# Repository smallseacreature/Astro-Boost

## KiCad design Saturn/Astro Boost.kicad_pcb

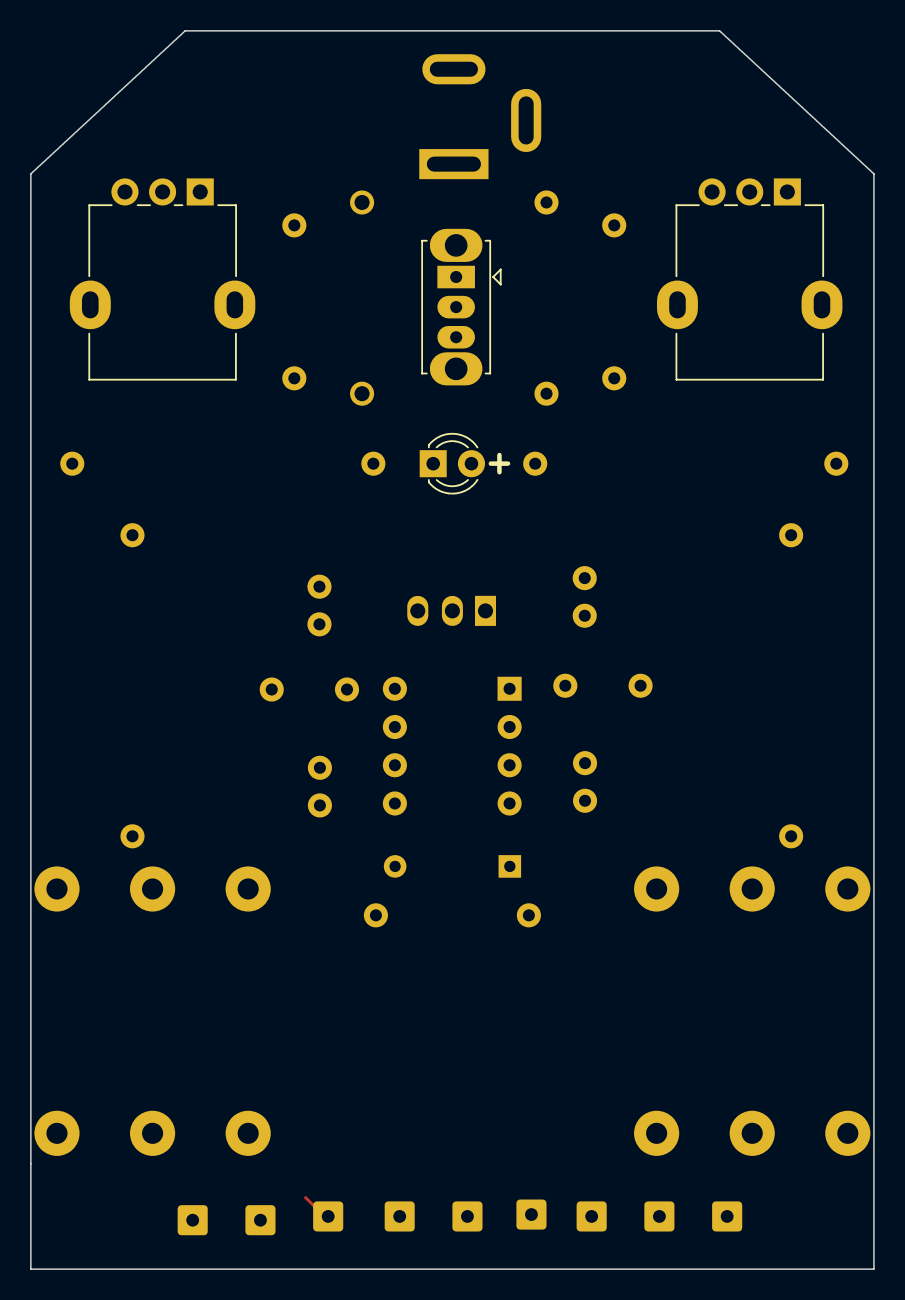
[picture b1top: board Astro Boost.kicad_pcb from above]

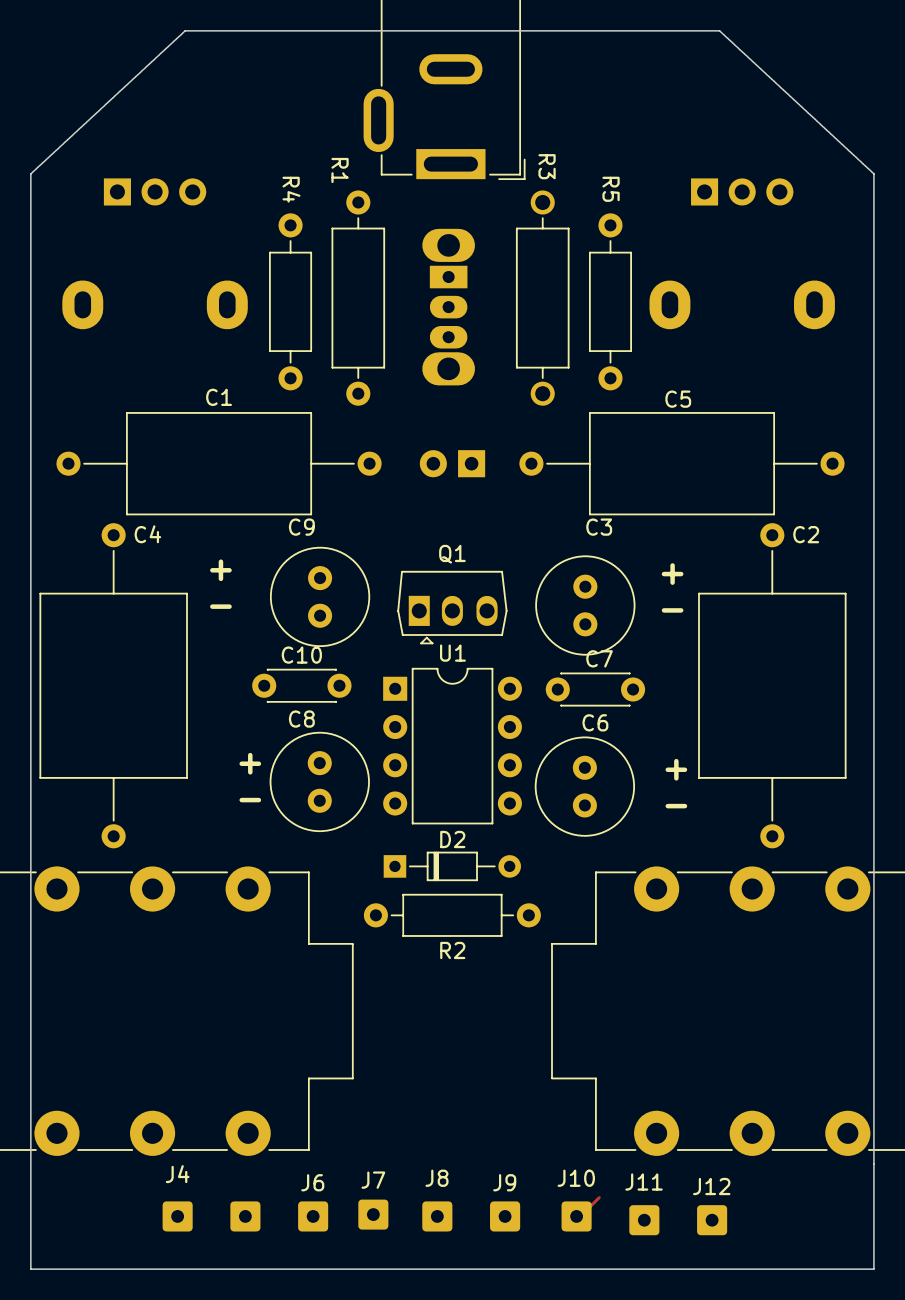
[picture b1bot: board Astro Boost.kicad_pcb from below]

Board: 2 copper layers, 56.0 x 82.2 mm, 35 parts (31 on the bottom side), 16 nets.

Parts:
BT1: 9V
C1, C5: 5n; C_Axial_L12.0mm_D6.5mm_P20.00mm_Horizontal
C2, C4: 10n; C_Axial_L12.0mm_D9.5mm_P20.00mm_Horizontal
C3, C6, C8, C9: 47u; C_Radial_D6.3mm_H11.0mm_P2.50mm
C7, C10: 100n; C_Disc_D4.3mm_W1.9mm_P5.00mm
D1: LED; LED_D3.0mm
D2: D1N4148; D_DO-34_SOD68_P7.62mm_Horizontal
J1, J2: AudioJack2; Jack_6.35mm_Neutrik_NMJ6HCD2_Horizontal
J3: Jack-DC; BarrelJack_GCT_DCJ200-10-A_Horizontal
J4: Signal In; SolderWire-0.25sqmm_1x01_D0.65mm_OD2mm
J5: Audio In; SolderWire-0.25sqmm_1x01_D0.65mm_OD2mm
J6: Processed to SW; SolderWire-0.25sqmm_1x01_D0.65mm_OD2mm
J7: Bypass; SolderWire-0.25sqmm_1x01_D0.65mm_OD2mm
J8: Processed Out; SolderWire-0.25sqmm_1x01_D0.65mm_OD2mm
J9: Power from 9V to SW; SolderWire-0.25sqmm_1x01_D0.65mm_OD2mm
J10: Power from SW to PS; SolderWire-0.25sqmm_1x01_D0.65mm_OD2mm
J11: +9V; SolderWire-0.25sqmm_1x01_D0.65mm_OD2mm
J12: -9V; SolderWire-0.25sqmm_1x01_D0.65mm_OD2mm
Q1: OC44; NEC_Molded_7x4x9mm
R1: 470; R_Axial_DIN0309_L9.0mm_D3.2mm_P12.70mm_Horizontal
R2, R4: 1M; R_Axial_DIN0207_L6.3mm_D2.5mm_P10.16mm_Horizontal
R3: 3.9K; R_Axial_DIN0309_L9.0mm_D3.2mm_P12.70mm_Horizontal
R5: 10K; R_Axial_DIN0207_L6.3mm_D2.5mm_P10.16mm_Horizontal
RV1: 10KA; Potentiometer_Alpha_RD901F-40-00D_Single_Vertical
RV2: 100K; Potentiometer_Alpha_RD901F-40-00D_Single_Vertical
SW1: SW_Nidec_CAS-120A1; SW_Slide_SPDT_Straight_CK_OS102011MS2Q
U1: MAX1044; DIP-8_W7.62mm

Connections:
0: C3.1, C8.1, C9.2, C10.1, D2.2 (A), J1.S, J2.S, J3.2, J12.1, R2.2, R3.2, R4.2, R5.2, RV2.2, RV2.3, U1.2 (CAP+), U1.3 (GND)
+9V: C6.1, C7.1, C9.1, C10.2, D1.2 (A), D2.1 (K), J10.1, U1.1 (NC), U1.8 (V+)
-9V: C6.2, C7.2, R1.1, RV1.1, U1.5 (VOUT)
Audio In: C1.2, J5.1, R4.1, SW1.2 (B)
unnamed: C2.2, RV1.2
unnamed: D1.1 (K), R5.1
unnamed: J1.T, J4.1
unnamed: J2.T, J7.1, J8.1
unnamed: C1.1, C4.1, C5.1, Q1.2 (B), R1.2, RV2.1
unnamed: Q1.1 (C), RV1.3
unnamed: C3.2, Q1.3 (E), R3.1
unnamed: C5.2, SW1.3 (A)
unnamed: C4.2, SW1.1 (C)
unnamed: C8.2, U1.4 (CAP-)
Power from 9V: J3.1, J9.1, J11.1
Processed to SW: C2.1, J6.1, R2.1

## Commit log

2024-11-30 Starter work
2024-11-30 Finished it
2024-12-01 renamed project 1 to jupiter
2024-12-18 Added Fix it list to jupiter
2024-12-18 updated fix it list
2024-12-23 Updates to Saturn
    Removed wiring pads and associated tracks
    Added to do list
    Shortened PCB
2024-12-24 Saturn PCB Updates
2024-12-25 updates to saturn
    layout
2024-12-26 Updates to saturn
